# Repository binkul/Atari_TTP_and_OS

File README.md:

# Tight Tools Packed and atari OS in one chip

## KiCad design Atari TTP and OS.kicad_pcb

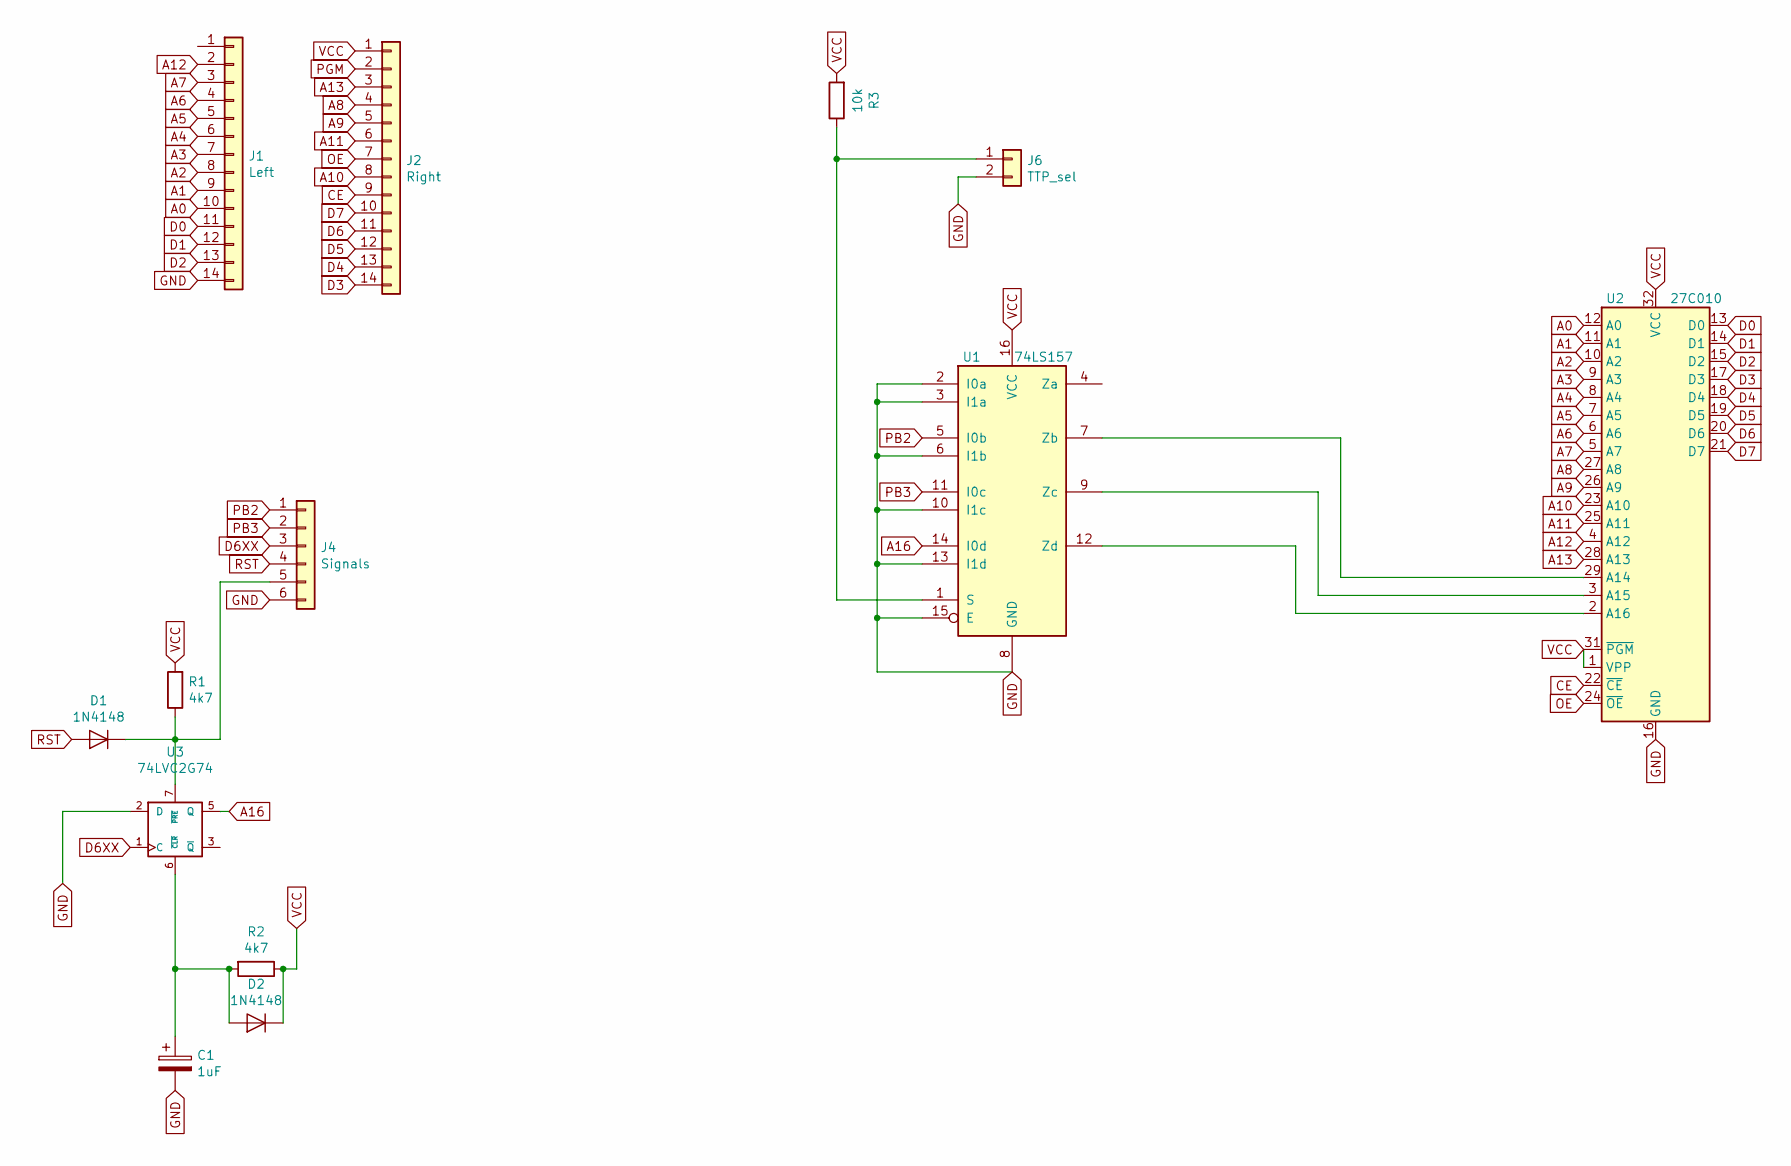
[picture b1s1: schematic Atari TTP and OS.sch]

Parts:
C1: 1uF; CP_Radial_D4.0mm_P1.50mm
D1, D2: 1N4148; D_1206_3216Metric_Pad1.42x1.75mm_HandSolder
J1: Left; PinHeader_1x14_P2.54mm_Vertical_thin
J2: Right; PinHeader_1x14_P2.54mm_Vertical_thin
J4: Signals; PinHeader_1x06_P2.54mm_Vertical
J6: TTP_sel; PinHeader_1x02_P2.54mm_Vertical
R1, R2: 4k7; R_1206_3216Metric_Pad1.42x1.75mm_HandSolder
R3: 10k; R_1206_3216Metric_Pad1.42x1.75mm_HandSolder
U1: 74LS157; SOIC-16_3.9x9.9mm_P1.27mm
U2: 27C010; PLCC-32_THT-Socket
U3: 74LVC2G74; TSSOP-8_3x3mm_P0.65mm

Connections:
A0: J1.10, U2.12 (A0)
A1: J1.9, U2.11 (A1)
A2: J1.8, U2.10 (A2)
A3: J1.7, U2.9 (A3)
A4: J1.6, U2.8 (A4)
A5: J1.5, U2.7 (A5)
A6: J1.4, U2.6 (A6)
A7: J1.3, U2.5 (A7)
A8: J2.4, U2.27 (A8)
A9: J2.5, U2.26 (A9)
A10: J2.8, U2.23 (A10)
A11: J2.6, U2.25 (A11)
A12: J1.2, U2.4 (A12)
A13: J2.3, U2.28 (A13)
A16: U1.14 (I0d), U3.5 (Q)
CE: J2.9, U2.22 (~CE)
D0: J1.11, U2.13 (D0)
D1: J1.12, U2.14 (D1)
D2: J1.13, U2.15 (D2)
D3: J2.14, U2.17 (D3)
D4: J2.13, U2.18 (D4)
D5: J2.12, U2.19 (D5)
D6: J2.11, U2.20 (D6)
D6XX: J4.3, U3.1 (C)
D7: J2.10, U2.21 (D7)
GND: C1.2, J1.14, J4.6, J6.2, U1.2 (I0a), U1.3 (I1a), U1.6 (I1b), U1.8 (GND), U1.10 (I1c), U1.13 (I1d), U1.15 (E), U2.16 (GND), U3.2 (D), U3.4 (GND)
unnamed: C1.1, D2.2 (A), R2.2, U3.6 (~CLR)
unnamed: D1.1 (K), J4.5, R1.1, U3.7 (~PRE)
unnamed: J6.1, R3.1, U1.1 (S)
unnamed: U1.7 (Zb), U2.29 (A14)
unnamed: U1.9 (Zc), U2.3 (A15)
unnamed: U1.12 (Zd), U2.2 (A16)
OE: J2.7, U2.24 (~OE)
PB2: J4.1, U1.5 (I0b)
PB3: J4.2, U1.11 (I0c)
RST: D1.2 (A), J4.4
VCC: D2.1 (K), J2.1, R1.2, R2.1, R3.2, U1.16 (VCC), U2.1 (VPP), U2.31 (~PGM), U2.32 (VCC), U3.8 (VCC)

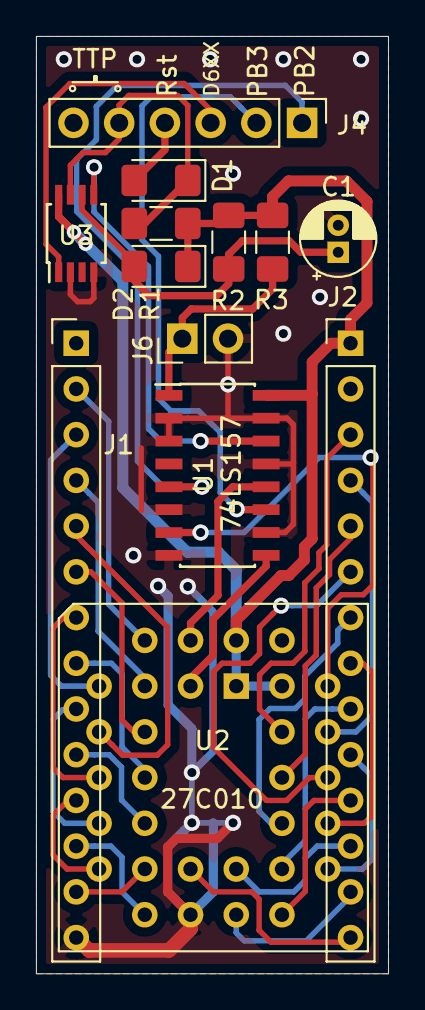
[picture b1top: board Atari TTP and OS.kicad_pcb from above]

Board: 2 copper layers, 19.6 x 52.1 mm, 13 parts (0 on the bottom side), 37 nets.

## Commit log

2021-03-09 Tracking
2021-03-18 origin master
